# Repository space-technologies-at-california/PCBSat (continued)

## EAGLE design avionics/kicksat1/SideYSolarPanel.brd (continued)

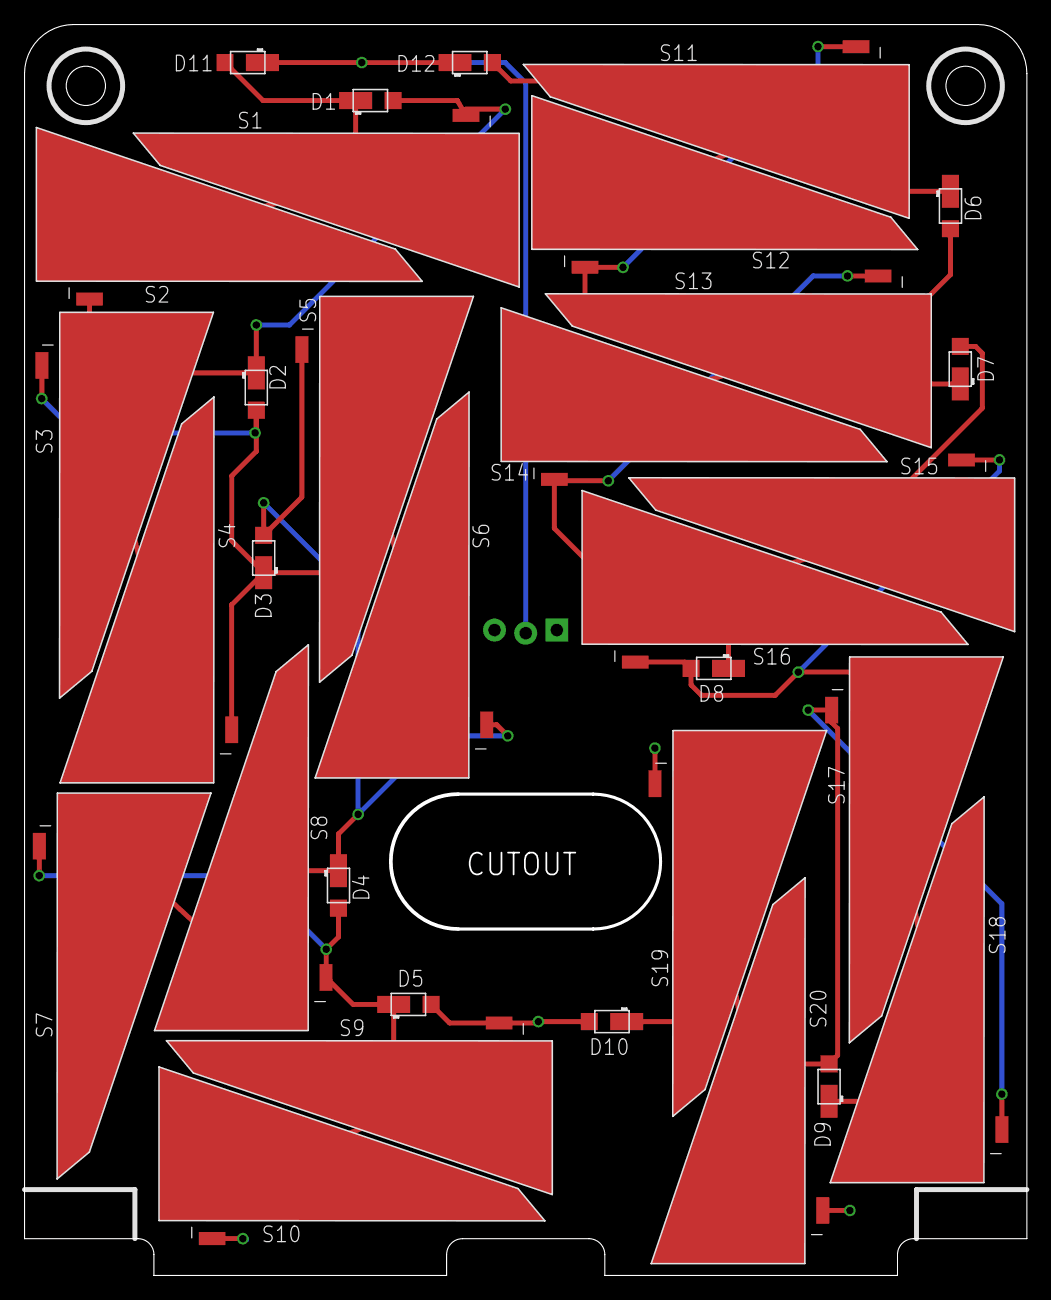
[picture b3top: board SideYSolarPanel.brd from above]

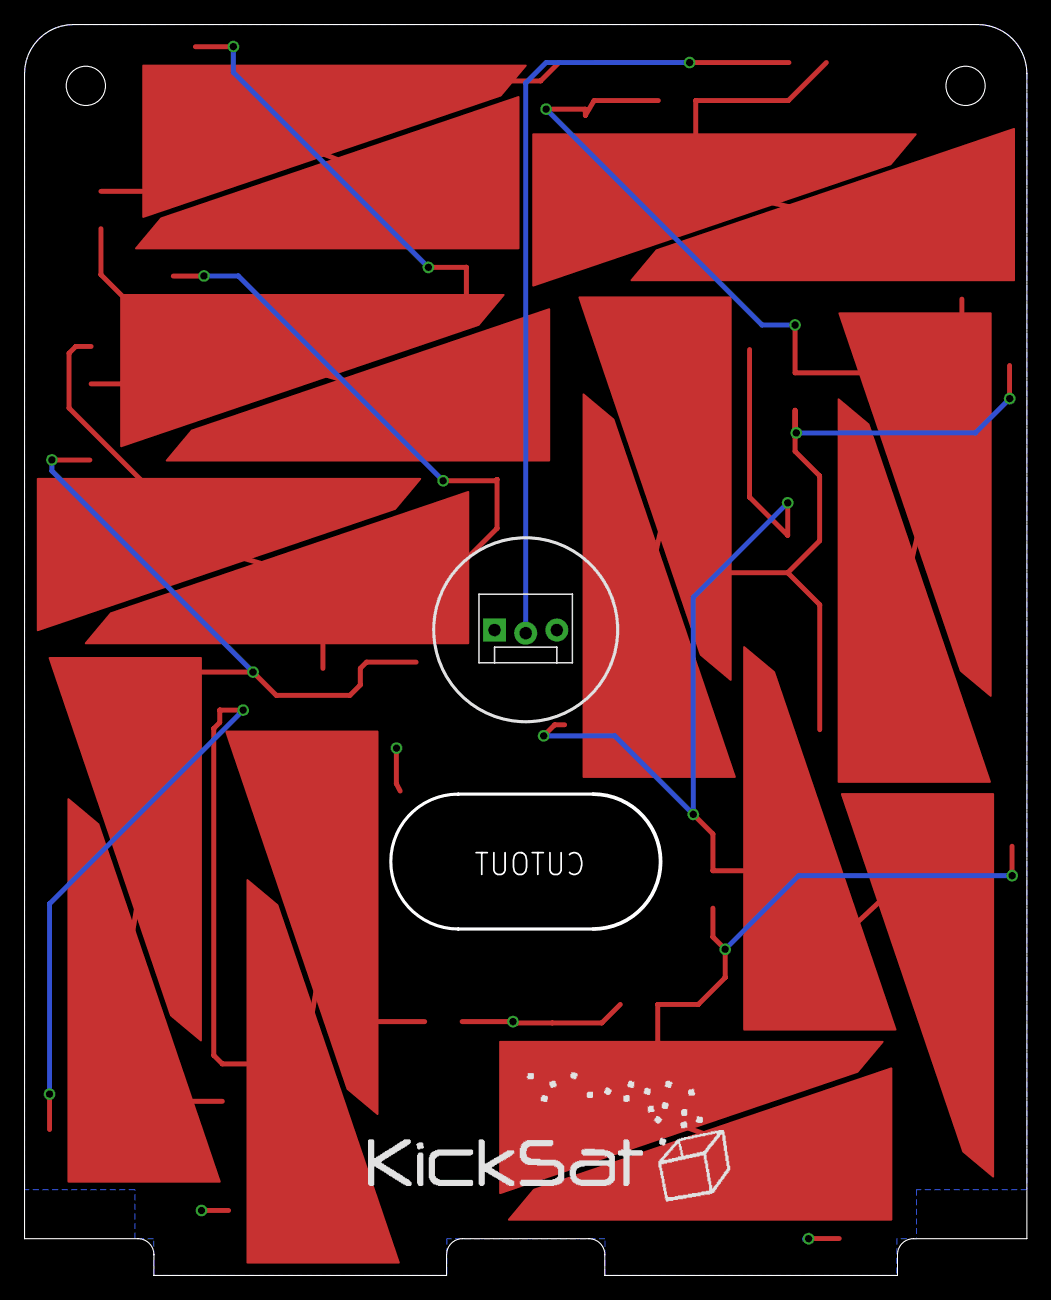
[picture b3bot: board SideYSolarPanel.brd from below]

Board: 2 copper layers, 81.7 x 102.0 mm, 35 parts (2 on the bottom side), 12 nets.

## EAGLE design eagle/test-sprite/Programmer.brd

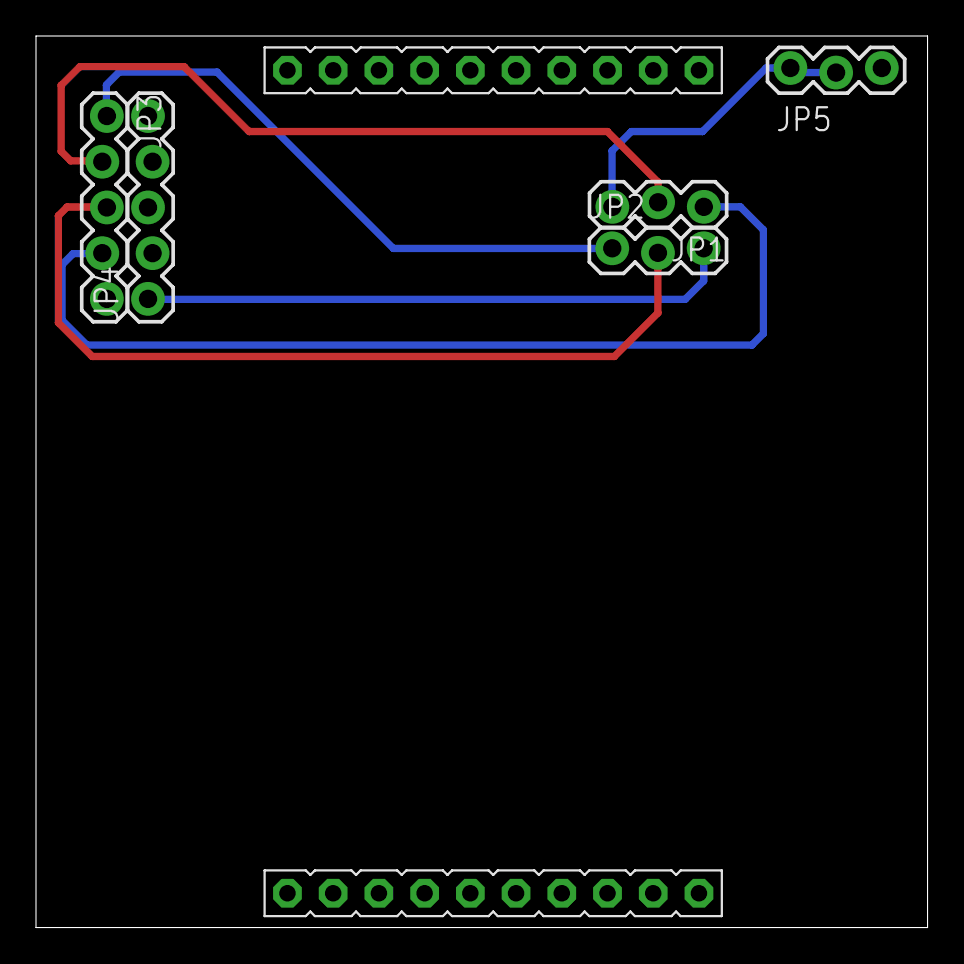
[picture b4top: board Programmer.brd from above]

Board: 2 copper layers, 49.5 x 49.5 mm, 6 parts (0 on the bottom side), 6 nets.

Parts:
JP1, JP2, JP5: 1X03_LOCK
JP3, JP4: 1X05_LOCK
U$1: LAUNCHPAD-50MM

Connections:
3.3V: JP2.1, JP3.1
GND: JP1.3, JP5.1, JP5.2, U$1.GND
RST: JP2.2, JP3.3
RXD: JP1.1, JP3.4
TEST: JP1.2, JP3.2
TXD: JP2.3, JP4.1

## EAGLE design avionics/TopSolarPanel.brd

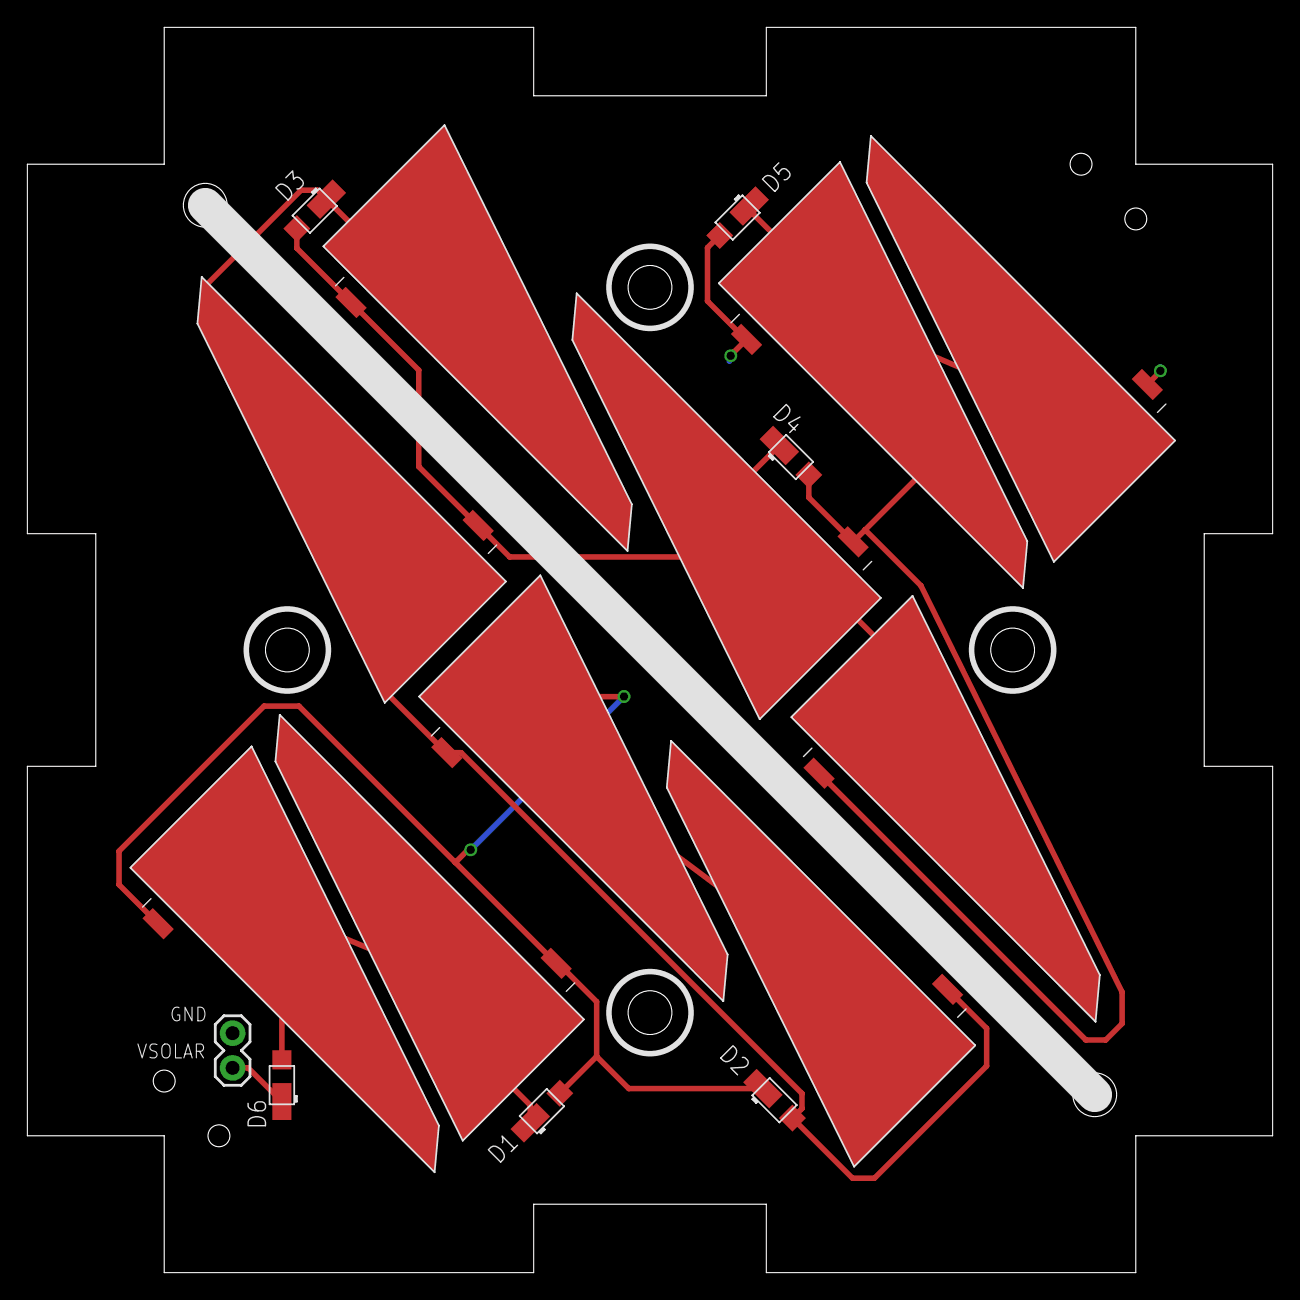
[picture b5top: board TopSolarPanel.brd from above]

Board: 2 copper layers, 91.0 x 91.0 mm, 19 parts (1 on the bottom side), 7 nets.

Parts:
D1, D2, D3, D4, D5, D6: SB_DIODE
FRAME1: FRAME-LETTER; CREATIVE_COMMONS
JP5: M02PTH; 1X02
SL1, SL2, SL3, SL4, SL5, SL6, SL7, SL8, SL9, SL10: SOLAR_CELL
U$1: KICKSAT_LOGO

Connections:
GND: D5.POS, JP5.1, SL9.1, SL10.1
unnamed: D1.NEG, D6.POS, SL1.2, SL2.2
unnamed: D2.POS, D3.NEG, SL3.1, SL4.1, SL5.2, SL6.2
unnamed: D3.POS, D4.NEG, SL5.1, SL6.1, SL7.2, SL8.2
unnamed: D1.POS, D2.NEG, SL1.1, SL2.1, SL3.2, SL4.2
unnamed: D4.POS, D5.NEG, SL7.1, SL8.1, SL9.2, SL10.2
VSOLAR: D6.NEG, JP5.2

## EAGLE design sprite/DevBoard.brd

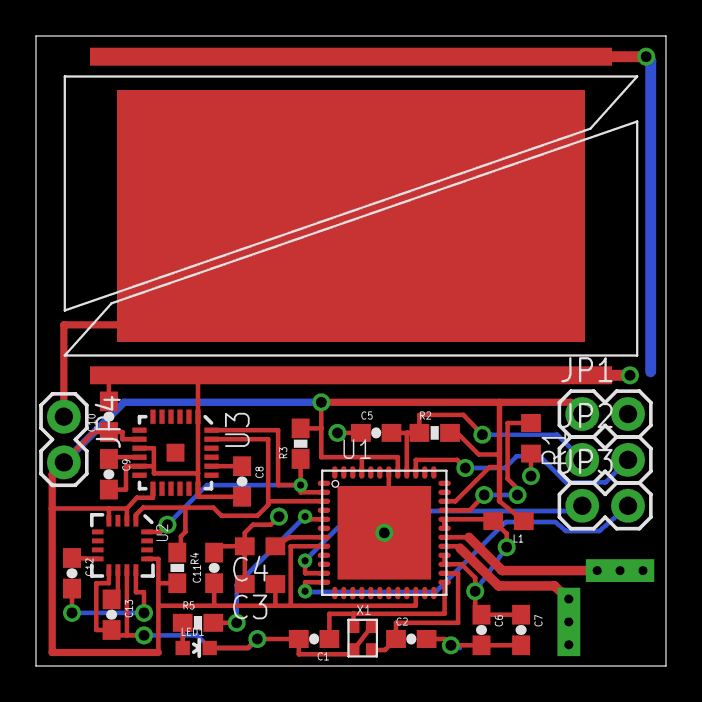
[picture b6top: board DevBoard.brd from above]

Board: 2 copper layers, 35.0 x 35.0 mm, 31 parts (0 on the bottom side), 23 nets.

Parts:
ANT-N: ANTENNA
ANT-P: ANTENNA
C1, C2: 27pF; 0603-CAP
C3, C4: 470nF; C0603
C5, C8: 2.2nF; 0603-CAP
C6, C9, C11: 100nF; 0603-CAP
C7, C10: 10nF; 0603-CAP
C12: 220nF; 0603-CAP
C13: 4.7uF; 0603-CAP
JP1, JP2, JP3, JP4: 1X02
L1: 12 nH; 0603
LED1: LED-0603
R1: 56K; R0603
R2: 47K; 0603-RES
R3, R4: 4.7K; 0603-RES
R5: 270R; 0603-RES
S1: TASC
U1: CC430F5137; RGZ48
U2: HMC5883LSMD; 16LPCC
U3: ITG-3200; QFN-24
X1: 26 MHz; ABM11_CERAMIC-SMD-CRYSTAL

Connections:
GND: C1.2, C2.2, C3.2, C4.2, C5.1, C6.2, C7.2, C8.2, C9.2, C10.2, C11.2, C13.2, JP1.2, LED1.C, R1.2, S1.MINUS1, S1.MINUS2, U1.42, U1.TP, U2.9, U2.11, U3.1, U3.9, U3.11, U3.18, X1.P$2, X1.P$4
unnamed: C2.1, U1.26, X1.P$3
unnamed: C1.1, U1.25, X1.P$1
unnamed: R1.1, U1.33
unnamed: C4.1, U1.7
unnamed: C12.1, U2.8
unnamed: C12.2, U2.12
unnamed: C13.1, U2.10
unnamed: C8.1, U3.20
unnamed: C9.1, U3.10
unnamed: R5.2, U1.5
unnamed: LED1.A, R5.1
RFN: ANT-N.IN1, ANT-N.IN2, ANT-N.IN3, U1.30
RFP: ANT-P.IN1, ANT-P.IN2, ANT-P.IN3, U1.29
RST: C5.2, JP2.1, R2.1, U1.40
RXD: JP3.2, U1.12
SCL: R4.1, U1.3, U2.1, U3.23
SDA: R3.1, U1.2, U2.16, U3.24
TEST: JP2.2, U1.39
TXD: JP3.1, U1.11
VCC: C3.1, C10.1, C11.1, JP1.1, JP4.2, L1.1, R2.2, R3.2, R4.2, U1.8, U1.22, U1.34, U1.41, U1.45, U2.2, U2.4, U2.13, U3.8, U3.13
VCCRF: C6.1, C7.1, L1.2, U1.27, U1.28, U1.31, U1.32
VSOLAR: JP4.1, S1.PLUS

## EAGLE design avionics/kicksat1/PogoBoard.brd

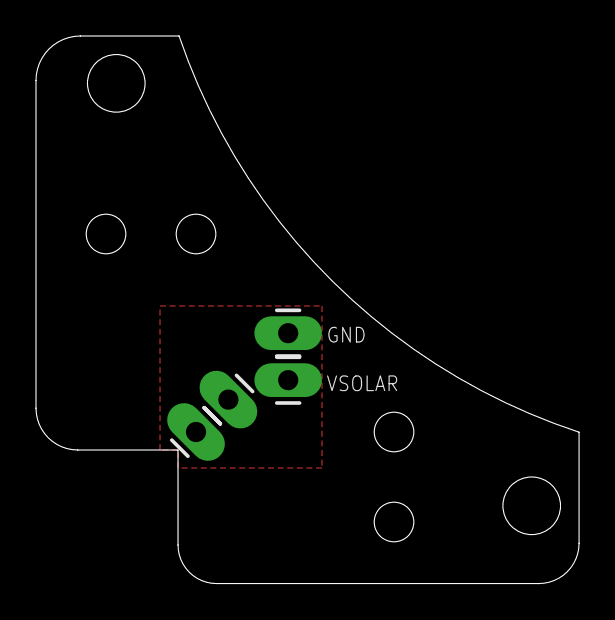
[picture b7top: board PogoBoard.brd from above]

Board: 2 copper layers, 30.2 x 30.4 mm, 5 parts (0 on the bottom side), 2 nets, no tracks yet.

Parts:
FRAME1: FRAME-LETTER; CREATIVE_COMMONS
JP1, JP2, JP3, JP4: M01PTH_LONGPAD; 1X01_LONGPAD

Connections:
GND: JP1.1, JP3.1
VSOLAR: JP2.1, JP4.1

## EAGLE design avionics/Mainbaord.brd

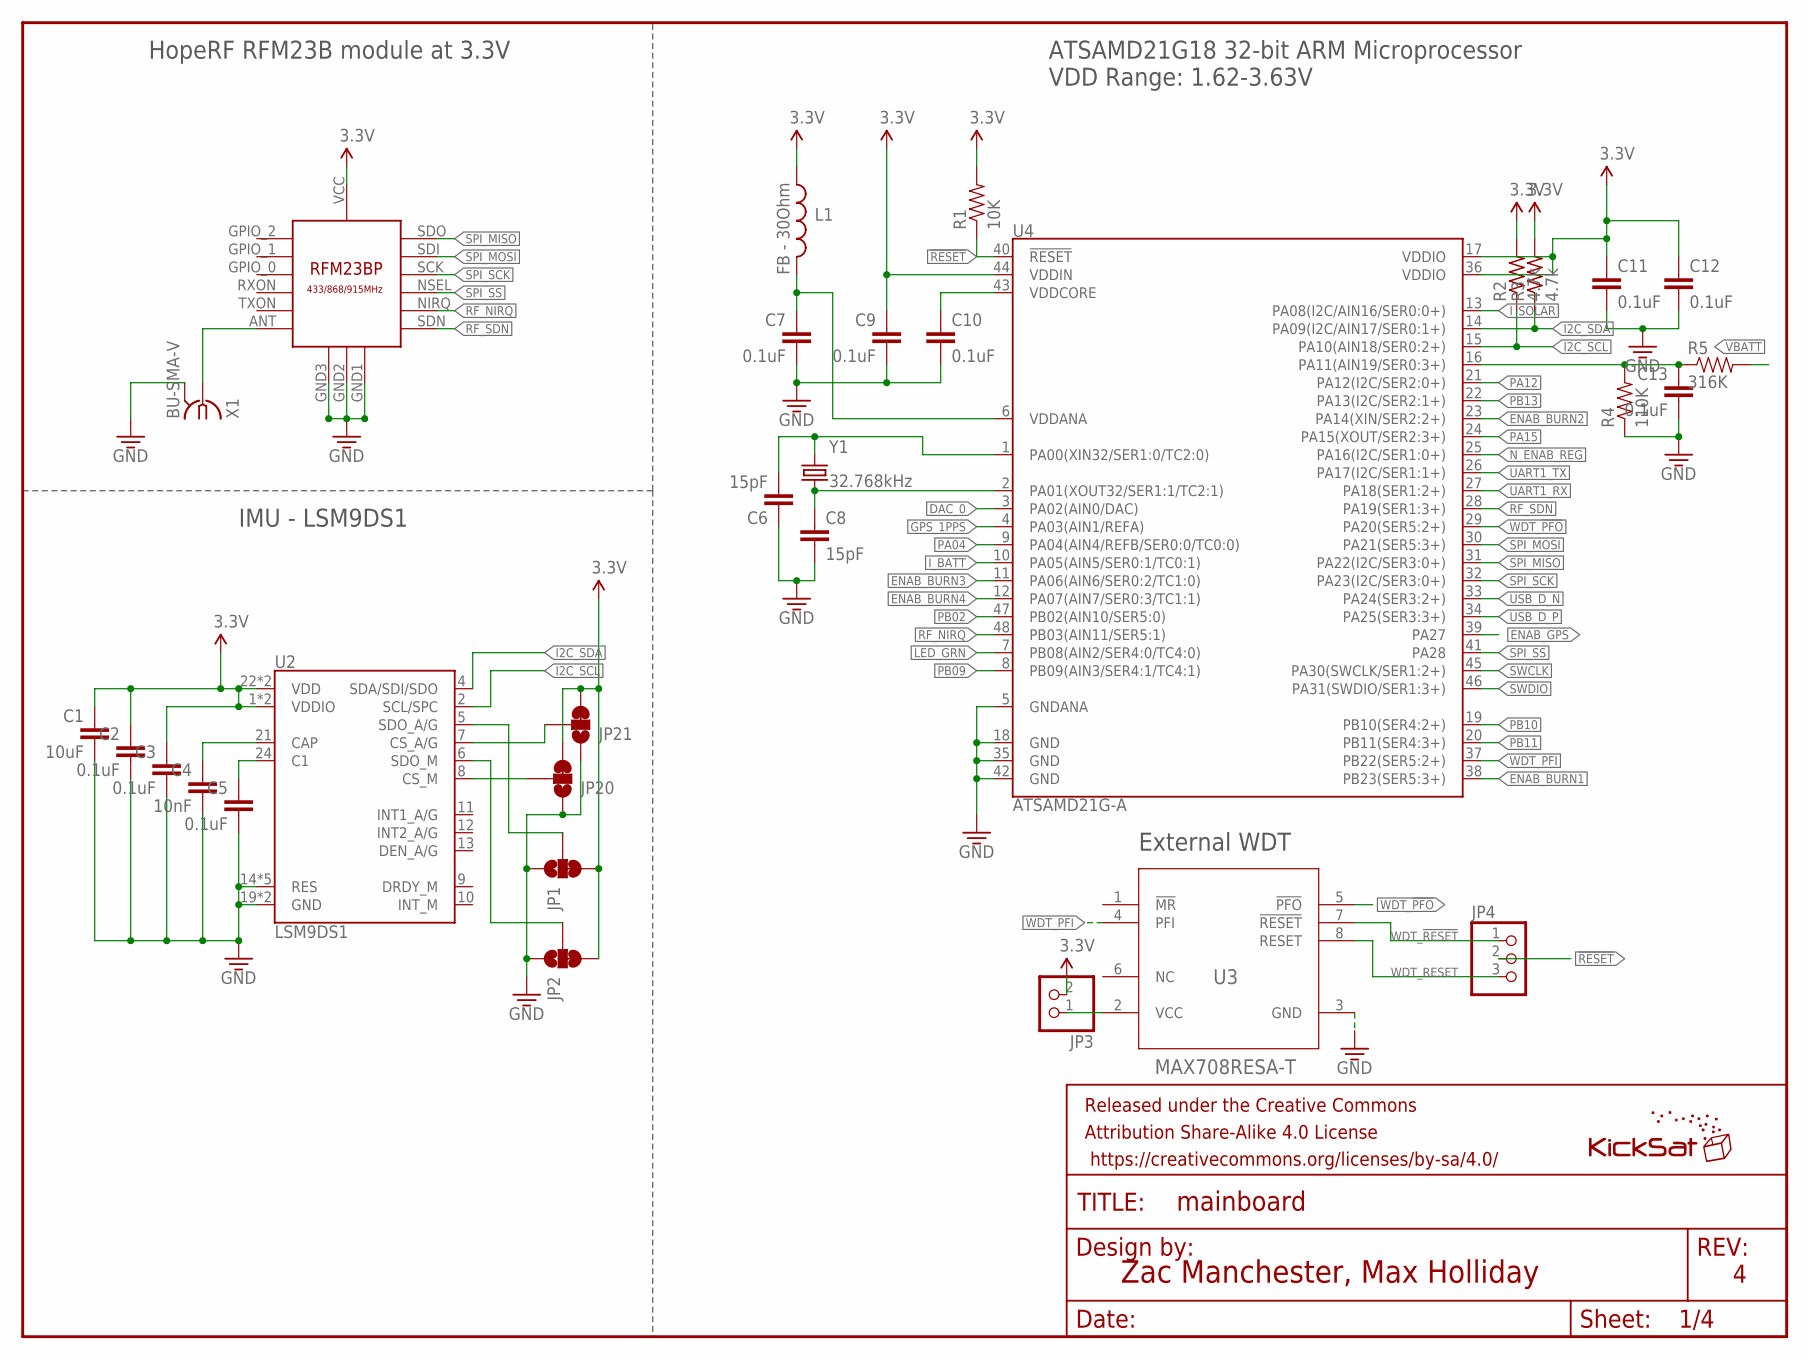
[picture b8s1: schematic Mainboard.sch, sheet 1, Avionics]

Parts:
C1: 10uF; 0603-CAP
C2, C3, C5, C7, C9, C10, C11, C12, C13: 0.1uF; 0603-CAP
C4: 10nF; 0603-CAP
C6, C8: 15pF; 0603-CAP@1
FRAME1: FRAME-LETTER; CREATIVE_COMMONS
JP1, JP2, JP20, JP21: JUMPER-PAD-3-2OF3_NC_BY_TRACE_SMALL; PAD-JUMPER-3-2OF3_NC_BY_TRACE_YES_SILK_FULL_BOX
JP3: PINHD-1X2; 1X02
JP4: PINHD-1X3; 1X03
L1: FB - 30Ohm; 0603
L2: KICKSAT_LOGO
R1: 10K; 0603-RES
R2, R3: 4.7k; R0603
R4: 110K; 0603-RES
R5: 316K; 0603-RES
U1: RFM23BP
U2: LSM9DS1; LGA24-8X4
U3: MAX708RESA-T; SO8
U4: ATSAMD21G-A; TQFP-48
X1: BU-SMA-V
Y1: 32.768kHz; CRYSTAL-SMD-3.2X1.5MM

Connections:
3.3V: C1.1, C2.1, C3.1, C9.1, C11.1, C12.1, JP1.3, JP2.3, JP3.2, JP20.3, JP21.3, L1.1, R1.2, R2.2, R3.2, U1.VCC, U2.1 (VDDIO), U2.3 (VDDIO), U2.22 (VDD), U2.23 (VDD), U4.17 (VDDIO), U4.36 (VDDIO), U4.44 (VDDIN); also elsewhere on the board
!RESET: JP4.2, R1.1, U4.40 (!RESET!); also elsewhere on the board
DAC_0: U4.3 (PA02(AIN0/DAC)); also elsewhere on the board
ENAB_BURN1: U4.38 (PB23(SER5:3+)); also elsewhere on the board
ENAB_BURN2: U4.23 (PA14(XIN/SER2:2+)); also elsewhere on the board
ENAB_BURN3: U4.11 (PA06(AIN6/SER0:2/TC1:0)); also elsewhere on the board
ENAB_BURN4: U4.12 (PA07(AIN7/SER0:3/TC1:1)); also elsewhere on the board
ENAB_GPS: U4.39 (PA27); also elsewhere on the board
GPS_1PPS: U4.4 (PA03(AIN1/REFA)); also elsewhere on the board
I2C_SCL: R2.1, U2.2 (SCL/SPC), U4.15 (PA10(AIN18/SER0:2+)); also elsewhere on the board
I2C_SDA: R3.1, U2.4 (SDA/SDI/SDO), U4.14 (PA09(I2C/AIN17/SER0:1+)); also elsewhere on the board
I2C_SDOA/G: JP1.2, U2.5 (SDO_A/G)
I_BATT: U4.10 (PA05(AIN5/SER0:1/TC0:1)); also elsewhere on the board
I_SOLAR: U4.13 (PA08(I2C/AIN16/SER0:0+)); also elsewhere on the board
LED_GRN: U4.7 (PB08(AIN2/SER4:0/TC4:0)); also elsewhere on the board
unnamed: C4.1, U2.21 (CAP)
unnamed: C5.1, U2.24 (C1)
unnamed: C7.1, L1.2, U4.6 (VDDANA)
unnamed: U1.ANT, X1.1
unnamed: JP2.2, U2.6 (SDO_M)
unnamed: JP20.2, U2.8 (CS_M)
unnamed: JP21.2, U2.7 (CS_A/G)
unnamed: C6.2, U4.1 (PA00(XIN32/SER1:0/TC2:0)), Y1.P$2 (2)
unnamed: C8.1, U4.2 (PA01(XOUT32/SER1:1/TC2:1)), Y1.P$1 (1)
unnamed: C13.1, R4.2, R5.1, U4.16 (PA11(AIN19/SER0:3+))
N_ENAB_REG: U4.25 (PA16(I2C/SER1:0+)); also elsewhere on the board
PA04: U4.9 (PA04(AIN4/REFB/SER0:0/TC0:0))
PA12: U4.21 (PA12(I2C/SER2:0+)); also elsewhere on the board
PA15: U4.24 (PA15(XOUT/SER2:3+))
PB02: U4.47 (PB02(AIN10/SER5:0)); also elsewhere on the board
PB09: U4.8 (PB09(AIN3/SER4:1/TC4:1)); also elsewhere on the board
PB10: U4.19 (PB10(SER4:2+)); also elsewhere on the board
PB11: U4.20 (PB11(SER4:3+)); also elsewhere on the board
PB13: U4.22 (PA13(I2C/SER2:1+))
RF_NIRQ: U1.NIRQ, U4.48 (PB03(AIN11/SER5:1))
RF_SDN: U1.SDN, U4.28 (PA19(SER1:3+))
SPI_MISO: U1.SDO, U4.31 (PA22(I2C/SER3:0+)); also elsewhere on the board
SPI_MOSI: U1.SDI, U4.30 (PA21(SER5:3+))
SPI_SCK: U1.SCK, U4.32 (PA23(I2C/SER3:0+)); also elsewhere on the board
SPI_SS: U1.NSEL, U4.41 (PA28)
SWCLK: U4.45 (PA30(SWCLK/SER1:2+)); also elsewhere on the board
SWDIO: U4.46 (PA31(SWDIO/SER1:3+)); also elsewhere on the board
UART1_RX: U4.27 (PA18(SER1:2+)); also elsewhere on the board
UART1_TX: U4.26 (PA17(I2C/SER1:1+)); also elsewhere on the board
USB_D_N: U4.33 (PA24(SER3:2+)); also elsewhere on the board
USB_D_P: U4.34 (PA25(SER3:3+)); also elsewhere on the board
VBATT: R5.2; also elsewhere on the board
VDDCORE3: C10.1, U4.43 (VDDCORE)
WDT_!PFO: U3.5 (!PFO), U4.29 (PA20(SER5:2+))
WDT_PFI: U3.4 (PFI), U4.37 (PB22(SER5:2+))
WDT_RESET: JP4.3, U3.8 (RESET)

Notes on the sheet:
Zac Manchester, Max Holliday
ATSAMD21G18 32-bit ARM Microprocessor VDD Range: 1.62-3.63V
HopeRF RFM23B module at 3.3V
IMU - LSM9DS1
External WDT

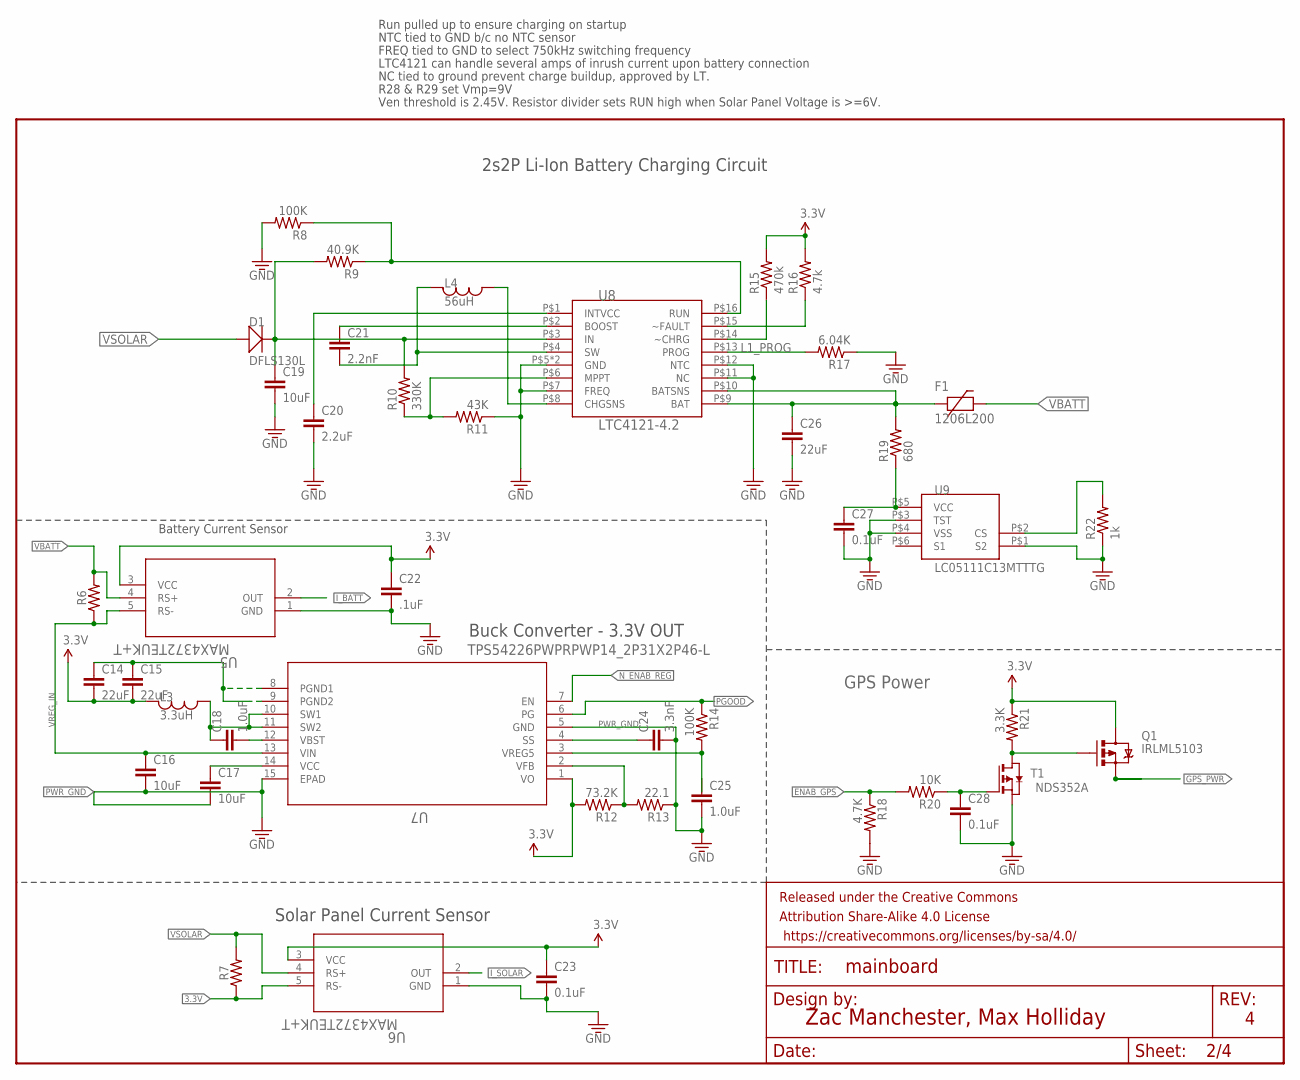
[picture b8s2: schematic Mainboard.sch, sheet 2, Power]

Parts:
C14, C15: 22uF; 0805
C16, C17, C19: 10uF; 0603
C18, C25: 1.0uF; 0603
C20: 2.2uF; 0603
C21: 2.2nF; 0603
C22: .1uF; 0603-CAP@1
C23, C27, C28: 0.1uF; 0603
C24: 3.3nF; 0603
C26: 22uF; 0603
D1: DFLS130L; PWRDI-123
F1: 1206L200; 1206
FRAME2: FRAME-LETTER; CREATIVE_COMMONS
L3: 3.3uH; 1812
L4: 56uH; 1812
Q1: IRLML5103; SOT23-3
R6, R7: 0603
R8, R14: 100K; R0603
R9: 40.9K; R0603
R10: 330K; R0603
R11: 43K; R0603
R12: 73.2K; R0603
R13: 22.1; R0603
R15: 470k; R0603
R16: 4.7k; R0603
R17: 6.04K; R0603
R18: 4.7K; R0603
R19: 680; R0603
R20: 10K; R0603
R21: 3.3K; R0603
R22: 1k; R0603
T1: NDS352A; SOT-23
U5, U6: MAX4372TEUK+T; 21-0057F
U7: TPS54226PWPRPWP14_2P31X2P46-L; PWP14_2P31X2P46-L
U8: LTC4121-4.2; QFN-16-PAD
U9: LC05111C13MTTTG; WDFN6

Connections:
3.3V: C14.2, C15.2, C22.1, C23.1, L3.P$1, Q1.3 (D), R7.1, R12.2, R15.2, R16.2, R21.1, U5.3 (VCC), U6.3 (VCC), U6.5 (RS-), U7.1 (VO); also elsewhere on the board
ENAB_GPS: R18.1, R20.2; also elsewhere on the board
GPS_PWR: Q1.2 (S); also elsewhere on the board
I_BATT: U5.2 (OUT); also elsewhere on the board
I_SOLAR: U6.2 (OUT); also elsewhere on the board
L1_CHG: R8.1, R9.1, U8.P$16 (RUN)
L1_FAULTN: R16.1, U8.P$15 (~FAULT)
L1_PROG: R17.2, U8.P$13 (PROG)
LION1: C26.1, F1.1, R19.2, U8.P$9 (BAT), U8.P$10 (BATSNS)
unnamed: C18.1, L3.P$2, U7.10 (SW1), U7.11 (SW2)
unnamed: C28.1, R20.1, T1.3 (G)
unnamed: Q1.1 (G), R21.2, T1.1 (D)
unnamed: C18.2, U7.12 (VBST)
unnamed: C21.2, L4.P$1, U8.P$4 (SW)
unnamed: C21.1, U8.P$2 (BOOST)
unnamed: C20.1, U8.P$1 (INTVCC)
unnamed: R10.1, R11.2, U8.P$6 (MPPT)
unnamed: L4.P$2, U8.P$8 (CHGSNS)
unnamed: R15.1, U8.P$14 (~CHRG)
unnamed: C27.1, R19.1, U9.P$5 (VCC)
unnamed: C17.1, U7.14 (VCC)
unnamed: R22.2, U9.P$2 (CS)
unnamed: C25.1, R14.2, U7.3 (VREG5)
unnamed: C24.1, U7.4 (SS)
unnamed: R12.1, R13.2, U7.2 (VFB)
N_ENAB_REG: U7.7 (EN); also elsewhere on the board
PGOOD: R14.1, U7.6 (PG)
PWR_GND: C14.1, C15.1, C16.2, C17.2, C24.2, C25.2, R13.1, U7.5 (GND), U7.8 (PGND1), U7.9 (PGND2), U7.15 (EPAD)
VBATT: F1.2, R6.2, U5.4 (RS+); also elsewhere on the board
VREG_IN: C16.1, R6.1, U5.5 (RS-), U7.13 (VIN)
VSOLAR: D1.A, R7.2, U6.4 (RS+); also elsewhere on the board
VSOLAR_IN: C19.1, D1.C, R9.2, R10.2, U8.P$3 (IN)

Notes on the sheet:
Solar Panel Current Sensor
Battery Current Sensor
Zac Manchester, Max Holliday
GPS Power
FREQ tied to GND to select 750kHz switching frequency
R28 & R29 set Vmp=9V
2s2P Li-Ion Battery Charging Circuit
Run pulled up to ensure charging on startup
NTC tied to GND b/c no NTC sensor
LTC4121 can handle several amps of inrush current upon battery connection
NC tied to ground prevent charge buildup, approved by LT.
Ven threshold is 2.45V. Resistor divider sets RUN high when Solar Panel Voltage is >=6V.
Buck Converter - 3.3V OUT

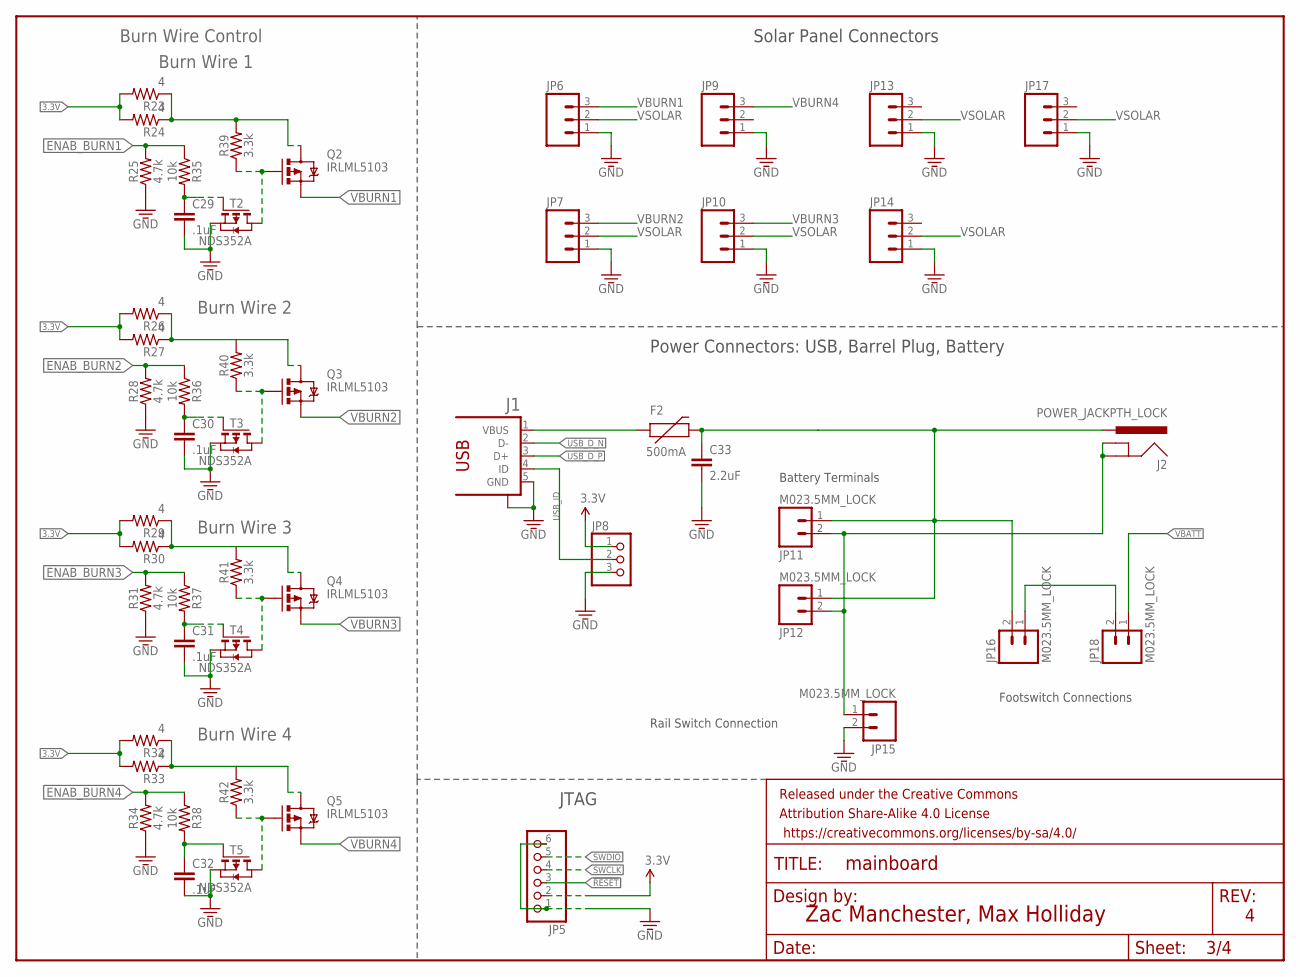
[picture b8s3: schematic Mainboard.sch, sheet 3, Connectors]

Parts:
C29, C30, C31, C32: .1uF; 0603-CAP@1
C33: 2.2uF; 0603
F2: 500mA; PTC-1206
FRAME3: FRAME-LETTER; CREATIVE_COMMONS
J1: 1981584-1
J2: POWER_JACKPTH_LOCK; POWER_JACK_PTH_LOCK
JP5: PINHD-1X6; 1X06
JP6, JP7, JP9, JP10, JP13, JP14, JP17: M03POLAR_LOCK; MOLEX-1X3_LOCK
JP8: PINHD-1X3; 1X03
JP11, JP12, JP15, JP16, JP18: M023.5MM_LOCK; SCREWTERMINAL-3.5MM-2_LOCK
Q2, Q3, Q4, Q5: IRLML5103; SOT23-3
R23, R24, R26, R27, R29, R30, R32, R33: 4; R0603
R25, R28, R31, R34: 4.7k; 0603
R35, R36, R37, R38: 10k; 0603
R39, R40, R41, R42: 3.3k; 0603
T2, T3, T4, T5: NDS352A; SOT-23

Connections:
3.3V: JP5.2, JP8.1, R23.2, R24.2, R26.2, R27.2, R29.2, R30.2, R32.2, R33.2; also elsewhere on the board
!RESET: JP5.3; also elsewhere on the board
ENAB_BURN1: R25.2, R35.1; also elsewhere on the board
ENAB_BURN2: R28.2, R36.1; also elsewhere on the board
ENAB_BURN3: R31.2, R37.1; also elsewhere on the board
ENAB_BURN4: R34.2, R38.1; also elsewhere on the board
unnamed: JP16.1, JP18.2
unnamed: C30.1, R36.2, T3.3 (G)
unnamed: Q2.1 (G), R39.1, T2.1 (D)
unnamed: C31.1, R37.2, T4.3 (G)
unnamed: F2.1, J1.1 (VBUS)
unnamed: Q3.1 (G), R40.1, T3.1 (D)
unnamed: J2.GND, J2.GNDBREAK, JP11.2, JP12.2, JP15.1
unnamed: C29.1, R35.2, T2.3 (G)
unnamed: C32.1, R38.2, T5.3 (G)
unnamed: Q4.1 (G), R41.1, T4.1 (D)
unnamed: Q5.1 (G), R42.1, T5.1 (D)
SWCLK: JP5.4; also elsewhere on the board
SWDIO: JP5.5; also elsewhere on the board
USB_D_N: J1.2 (D-); also elsewhere on the board
USB_D_P: J1.3 (D+); also elsewhere on the board
USB_ID: J1.4 (ID), JP8.2
VBATT: C33.1, F2.2, J2.PWR, JP11.1, JP12.1, JP16.2, JP18.1; also elsewhere on the board
VBURN1: JP6.3, Q2.2 (S)
VBURN2: JP7.3, Q3.2 (S)
VBURN3: JP10.3, Q4.2 (S)
VBURN4: JP9.3, Q5.2 (S)
VBURN_IN: Q2.3 (D), Q3.3 (D), Q4.3 (D), Q5.3 (D), R23.1, R24.1, R26.1, R27.1, R29.1, R30.1, R32.1, R33.1, R39.2, R40.2, R41.2, R42.2
VSOLAR: JP6.2, JP7.2, JP10.2, JP13.2, JP14.2, JP17.2; also elsewhere on the board

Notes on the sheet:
Footswitch Connections
Solar Panel Connectors
Battery Terminals
Rail Switch Connection
Zac Manchester, Max Holliday
JTAG
Power Connectors: USB, Barrel Plug, Battery
Burn Wire 1
Burn Wire Control
Burn Wire 2
Burn Wire 3
Burn Wire 4

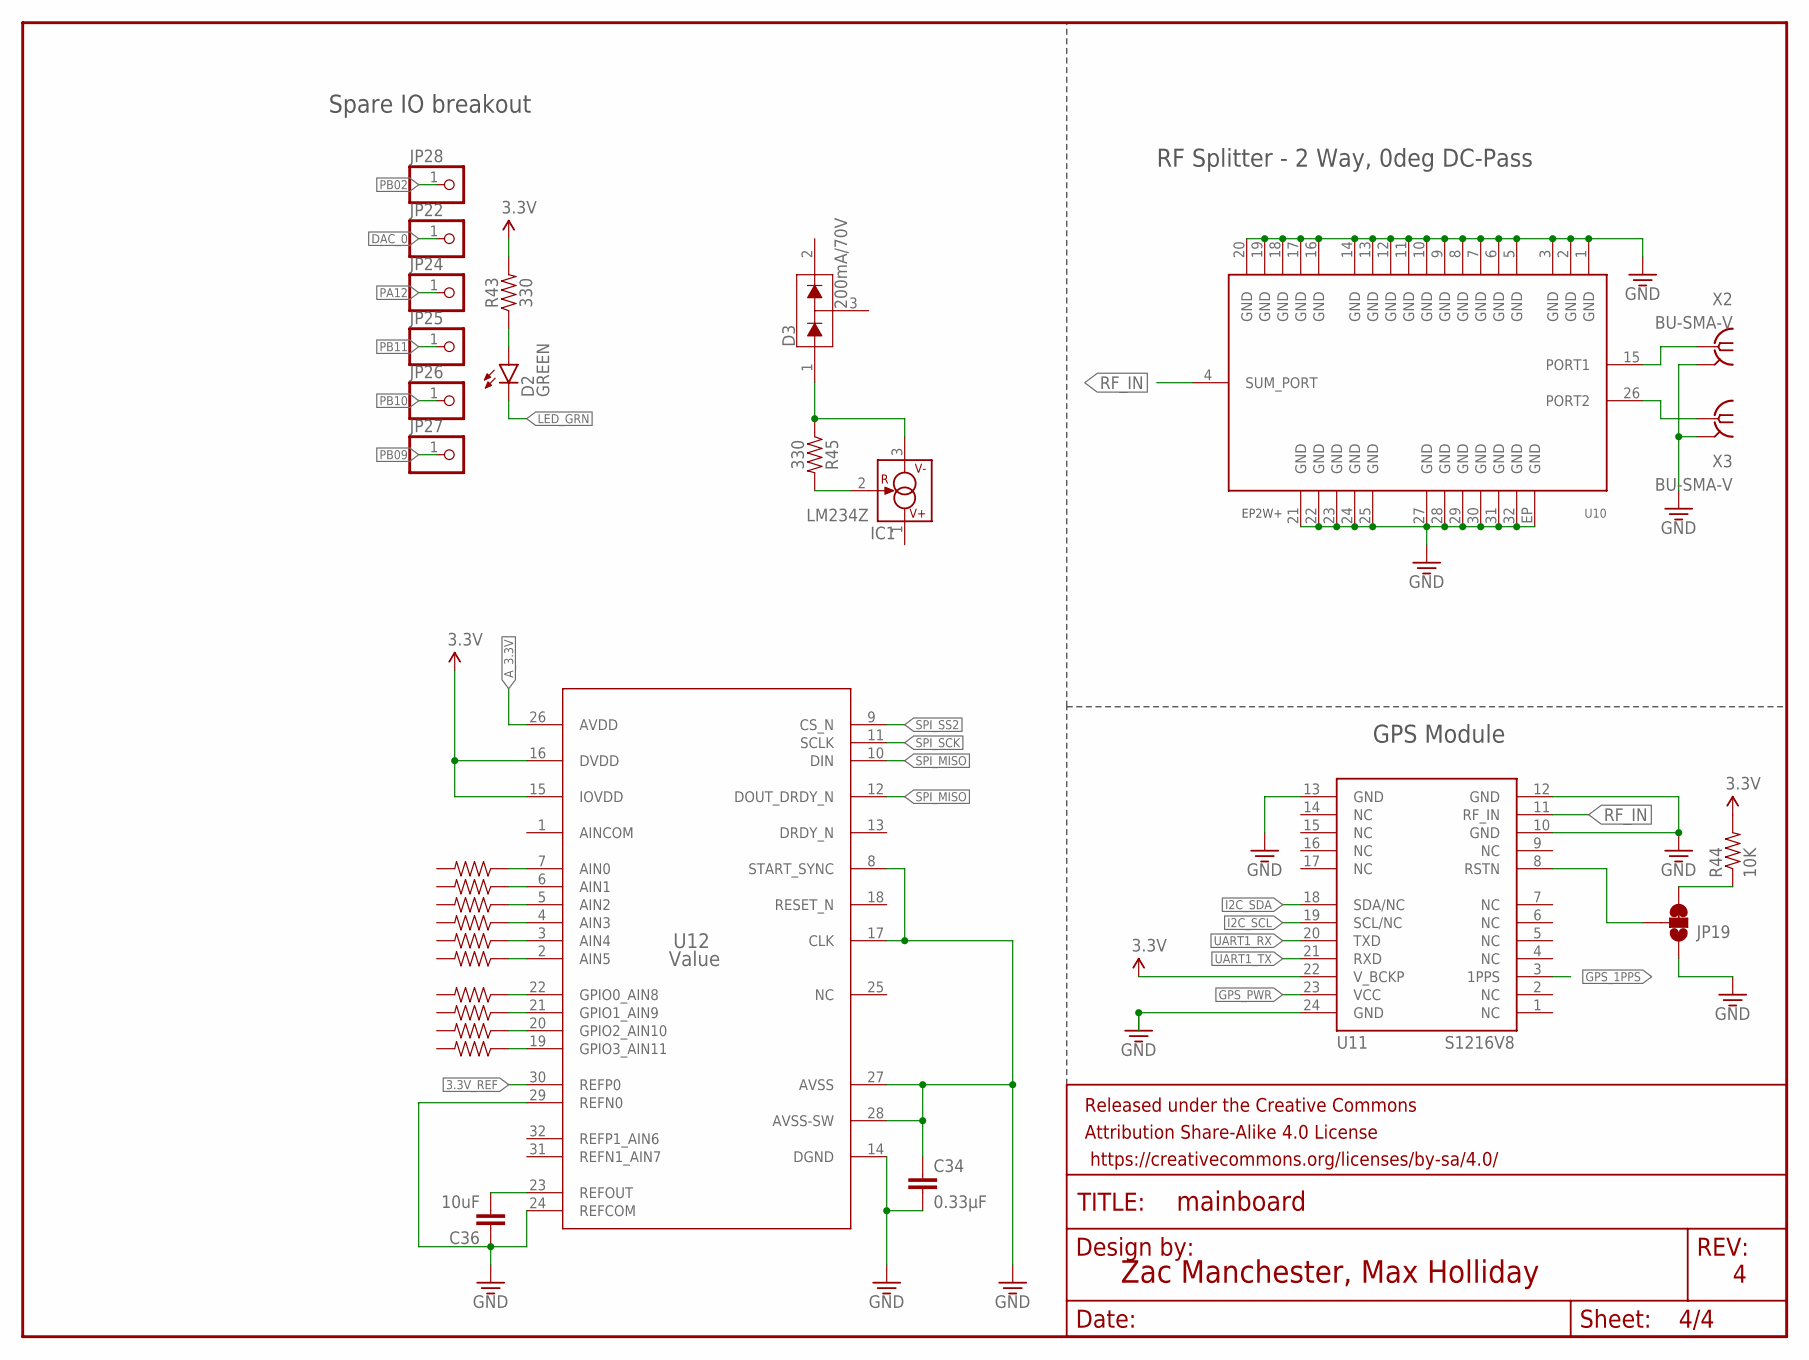
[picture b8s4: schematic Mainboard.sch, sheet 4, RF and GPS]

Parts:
C34: 0.33µF; 0805
C36: 10uF; 0603
D2: GREEN; LED-0603
D3: 200mA/70V; SOT23-3
FRAME4: FRAME-LETTER; CREATIVE_COMMONS
IC1: LM234Z; TO92
JP19: JUMPER-PAD-3-2OF3_NC_BY_TRACE_SMALL; PAD-JUMPER-3-2OF3_NC_BY_TRACE_YES_SILK_FULL_BOX
JP22, JP24, JP25, JP26, JP27, JP28: PINHD-1X1; 1X01
R43, R45: 330; 0603-RES
R44, R46, R47, R48, R49, R50, R51, R52, R53, R54, R55: 10K; 0603-RES
U10: EP2W+; QFN32-5X5MM
U11: S1216V8; S1216_24PIN_PACKAGE
U12: Value; PBS0032A_N
X2, X3: BU-SMA-V

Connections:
3.3V: R43.2, R44.2, U11.22 (V_BCKP), U12.15 (IOVDD), U12.16 (DVDD); also elsewhere on the board
3.3V_REF: U12.30 (REFP0)
A_3.3V: U12.26 (AVDD)
DAC_0: JP22.1; also elsewhere on the board
GPS_1PPS: U11.3 (1PPS); also elsewhere on the board
GPS_PWR: U11.23 (VCC); also elsewhere on the board
I2C_SCL: U11.19 (SCL/NC); also elsewhere on the board
I2C_SDA: U11.18 (SDA/NC); also elsewhere on the board
LED_GRN: D2.C; also elsewhere on the board
unnamed: D2.A, R43.1
unnamed: JP19.2, U11.8 (RSTN)
unnamed: U10.15 (PORT1), X2.1
unnamed: U10.26 (PORT2), X3.1
unnamed: R47.1, U12.7 (AIN0)
unnamed: JP19.3, R44.1
unnamed: R48.1, U12.6 (AIN1)
unnamed: R49.1, U12.5 (AIN2)
unnamed: IC1.2 (R), R45.2
unnamed: D3.1 (A1), IC1.3 (V-), R45.1
unnamed: R50.1, U12.4 (AIN3)
unnamed: R51.1, U12.3 (AIN4)
unnamed: R52.1, U12.2 (AIN5)
unnamed: R46.1, U12.22 (GPIO0_AIN8)
unnamed: R53.1, U12.21 (GPIO1_AIN9)
unnamed: C36.2, U12.23 (REFOUT)
unnamed: R54.1, U12.20 (GPIO2_AIN10)
unnamed: R55.1, U12.19 (GPIO3_AIN11)
PA12: JP24.1; also elsewhere on the board
PB02: JP28.1; also elsewhere on the board
PB09: JP27.1; also elsewhere on the board
PB10: JP26.1; also elsewhere on the board
PB11: JP25.1; also elsewhere on the board
RF_IN: U10.4 (SUM_PORT), U11.11 (RF_IN)
SPI_MISO: U12.10 (DIN), U12.12 (DOUT_DRDY_N); also elsewhere on the board
SPI_SCK: U12.11 (SCLK); also elsewhere on the board
SPI_SS2: U12.9 (CS_N)
UART1_RX: U11.20 (TXD); also elsewhere on the board
UART1_TX: U11.21 (RXD); also elsewhere on the board

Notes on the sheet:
GPS Module
RF Splitter - 2 Way, 0deg DC-Pass
Zac Manchester, Max Holliday
Spare IO breakout
